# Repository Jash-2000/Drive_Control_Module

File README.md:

# Drive_Control_Module
Designed and Developed the Drive Control module for an Formula Electric car using ARM cortex processor.

---

## CAN - Controller Area Network

CAN provides four different types of message frames:

1. Data Frame – Sends data
Data transfer from one sending node to one or numerous receiving nodes.

2. Remote Frame – Requests data

Any node may request data from one source node. A remote frame is consequently followed by a data frame containing the requested data.

3. Error Frame – Reports error condition
Any bus participant, sender or receiver, may signal an error condition at any time during a data or remote frame transmission.

4. Overload Frame – Reports node overload

A node can request a delay between two data or remote frames, meaning that the overload frame can only occur between data or remote frame transmissions.

---

## Topics 

Vehicle Dynamics
```
  Wheel alignment
  Roll, yaw, pitch
  ABS
  Types of suspension, braking, brake fluid
  UV joints, rack & pinion
  Oversteer, understeer, counter-steer
  Load transfer
  Bearings
```

Aerodynamics
```
Lift & Drag (types and causes)
Centre of pressure
Coanda effect
Ground effect
Basic Airfoil terminology
Chassis and Ergonomics
Chassis Flex
Chassis stiffness
Different types of chassis
Composites used for making chassis
```

Powertrain
```
Thermodynamic cycles in engine.
All parts of engine, intake, exhaust.
Restrictor
Compression Ratio
Knocking
Torque steer elimination
CV and other types of joints
Differential: working and need
Volumetric efficiency
Chain tensioning methods
Engine tuning parameters
```

Electronics and Safety Circuits
```
Sensors
DAQ (Data Acquisition System)
T-MAP sensors
Relays
Solenoids
Shutdown/kill switches
Rectifier
Diodes
Motor and Controller
Types and working of electric motors
Torque Vectoring
Functions of motor controller
```

Battery and Battery Management System
```
Regenerative Braking
Cell Balancing, Charging/discharging profiles of battery
Power, energy density of cells
Heating and methods of temperature control
```

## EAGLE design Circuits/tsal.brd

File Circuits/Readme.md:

This file contains the Low voltage circuitary developed in order to aid the functionalities of the car. The PCB designing and routing files as well as the associated gerber files
are present here.

  * BSPD - Brake System Pausiblity Device - This Safety Critical Signal uses a pressure sensor and shuts down the car in case of hard braking. It is also integrated with the DCM
for the purpose of logitics and also cutting down the signal for torque as well.
  * IMD - Insulation Monitoring device - This device esures that 2 different lines of voltage have no leakage current.
  * TSAL - The Tractive System Active Light is a red/green indicator light that indicates the presence of high-voltage in the Tractive System. The following design for a TSAL driver is split across two modules. The High-Voltage Measurement module (HVM) and the Indicator Module (DRV). The HVM connects to the output of the AIRs, and is located in the accumulator housing. The HVM is responsible for detecting whether Tractive System voltage is above or below the safe threshold.
  * Prechargs Circuit - A device to precharge the Tractive System. This prototype features voltage feedback to protect AIRs. In open-loop systems, if a wiring fault develops (eg. precharge resistor is disconnected or discharge is stuck on) then the precharge is ineffective and AIRs may become damaged.

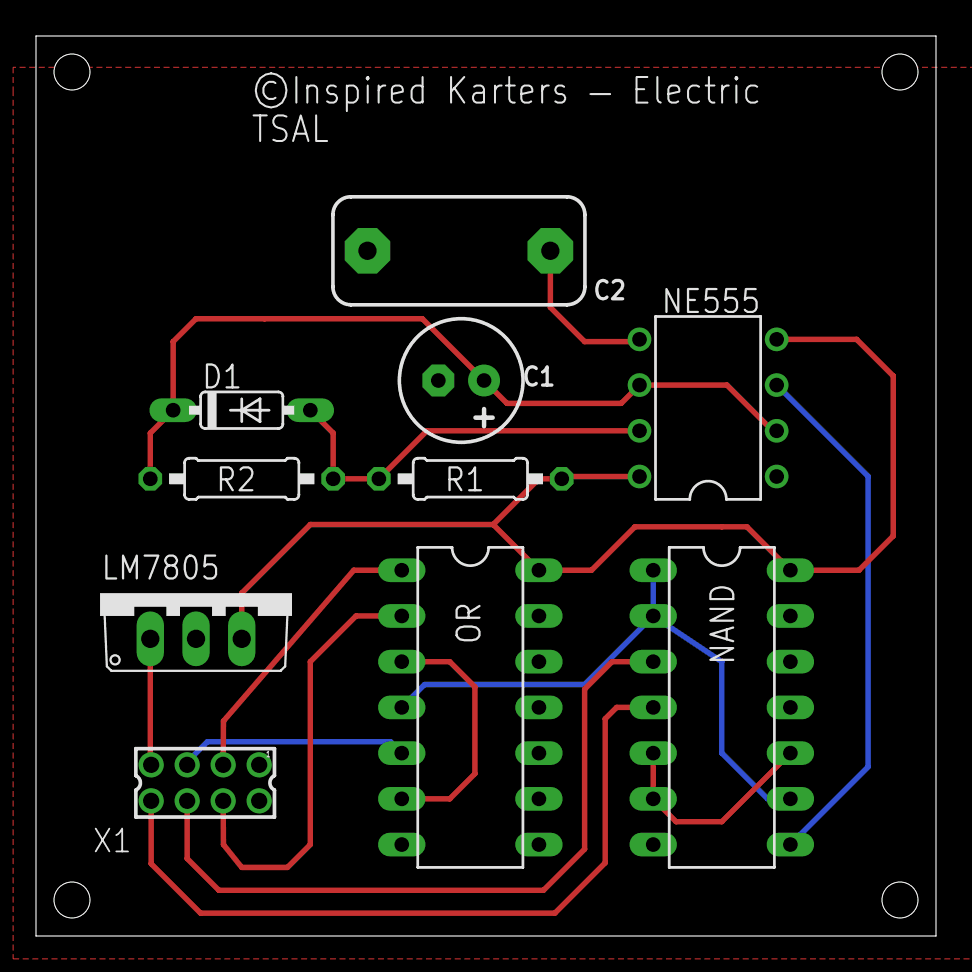
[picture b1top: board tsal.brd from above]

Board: 2 copper layers, 50.0 x 50.0 mm, 10 parts (0 on the bottom side), 15 nets.

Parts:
C1: 1µF; CE-025X060
C2: 0.01µF; C100-140X060
D1: 1N4148DO35-7; DO35-7
LM7805: 7805TV; TO220V
NAND: 4011N; DIL14
NE555: NE555N; DIL08
OR: 4071N; DIL14
R1, R2: 220kΩ; 0207/10
X1: 87758-0816

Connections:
GND: C1.-, C2.2, LM7805.2, NAND.7, NE555.1, OR.7, X1.2
unnamed: OR.1, X1.3
unnamed: OR.2, X1.4
unnamed: OR.3, OR.6
unnamed: OR.5, X1.5
unnamed: NAND.1, NAND.2, NAND.9, OR.4
unnamed: NAND.3, X1.6
unnamed: D1.A, NE555.7, R1.2, R2.1
unnamed: C1.+, D1.C, NE555.2, NE555.6, R2.2
unnamed: C2.1, NE555.5
unnamed: NAND.5, NAND.6, NAND.10
unnamed: NAND.4, X1.8
unnamed: NAND.8, NE555.3
VCC: LM7805.1, X1.7
VO: LM7805.3, NAND.14, NE555.4, NE555.8, OR.14, R1.1

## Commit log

2021-03-02 Added Procurement Report
2021-06-11 Added the circuit files
2021-06-11 Additional PCBs added
2021-06-11 Added Concept challenge report
2021-06-11 Create Manual
2021-06-12 Safety Circuit
2021-06-12 Control file reference
2021-07-30 Design files added

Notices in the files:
Circuits/tsal.brd:
©Inspired Karters — Electric
parts and their libraries:
rc-master: Copyright (C) 2007, Bob Starr
